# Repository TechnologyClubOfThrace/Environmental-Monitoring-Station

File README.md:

### Περιβαλλοντικός σταθμός επιτήρησης

Ο περιβαλλοντικός σταθμός επιτήρησης ειναι μια κατασκευή βασισμένη στο arduino και σε ανοιχτές τεχνολογίες με σκοπό την καταγραφή περιβαλλοντικών μετρήσεων, όπως ενδεικτικά, η ποιότητα του αέρα που αναπνέουμε, η καθαρότητα του νερού που πίνουμε, τα επίπεδα της ραδιενέργειας και η ηλεκτρομαγνητική ακτινοβολία.

Στην Ελλάδα πέρα απο κάποιες μετρήσεις για την ατμοσφαιρική ρύπανση που γίνονται κυρίως στην Αθήνα και την θεσσαλονίκη, δεν γνωρίζουμε σε πραγματικό χρόνο τι συμβαίνει στην ατμόσφαιρα.

Καθώς αναπτύσουμε τον σταθμό, ανεβάζουμε και τα δεδομένα που συλλέγονται από τους αισθητήρες εδώ: [Environmental Monitoring Station Live Experimental URL](http://iot.techthrace.com:8080/dashboard/c0007be0-88fe-11eb-8796-2726fafed088?publicId=e1c6fd00-e92f-11e9-a846-0761562e699c)

### Το hardware
Η κατασκευή βασίζεται στο [ESP32-DevKitC](https://www.espressif.com/en/products/hardware/development-boards "ESP32-DevKitC") που εχει ενσωματωμένο WiFi ώστε να μπορούμε να αποστείλουμε τα δεδομένα στον [Thingboard IoT server](https://thingsboard.io/ "Thingboard IoT server"). Όλοι οι αισθητήρες που ενδέχεται να χρησιμοποιηθούν βρίσκονται στην ενότητα [Προμήθεια Hardware](#προμήθεια-hardware)

###### Ενδεικτικά κάποιοι αισθητήρες που θα χρησιμοποιηθούν:

    Αισθητήρας μικρόσωματιδίων MP 10 και MP 2.5
    Αισθητήρας αζώτου
    Αισθητήρας διοξειδίου του άνθρακα
    Αισθητήρας μονοξειδίου του άνθρακα
    Αισθητήρας UV ακτινοβολίας
    Αισθητήρας θερμοκρασίας
    Αισθητήρας υγρασίας
    Αισθητήρας ατμοσφαιρικής πίεσης 

Οταν θα εχει ολοκληρωθεί η σύνδεση των αισθητήρων θα δημοσιεύσουμε εδώ αναλυτικές οδηγίες σχετικά με τον τρόπο σύνδεσης στο ESP32 ώστε να μπορει οποίος θέλει να κατασκευάσει τον δικό του σταθμό και αν θέλει να στέλνει τα δεδομένα στον υπάρχον IoT server για να εχουμε μια ακομα καλύτερη εικόνα του περιβάλλοντος απο διάφορες περιοχές.

### Το software 
Ο κώδικας που τρέχει στο ESP32 βρίσκεται μέσα στο φάκελο [src/EnvironmentalMonitoringStation](https://github.com/TechnologyClubOfThrace/Environmental-Monitoring-Station/tree/master/src/EnvironmentalMonitoringStation "src/EnvironmentalMonitoringStation") και μπορείτε να τον ανοίξετε με το Arduino IDE.

Για να γινει compile θα πρεπει να εγκαταστήσετε αρχικά τους οδηγούς για το ESP32 και στη συνεχεια και όλα τα header files που θα σας εμφανίσει οτι λείπουν το Arduino IDE. Τα header files θα πρεπει να τα αντιγράψετε απο τον φάκελο arduino_libraries μέσα στο φάκελο libraries του Arduino IDE. Την τοπική διαδρομή στο μηχάνημα σας μπορείτε να την δείτε απο τα preferences του Arduino IDE.

Πέρα απο το λογισμικό που τρέχει μέσα στο ESP32, υπάρχει και το server side κομμάτι όπου συλλέγονται και παρουσιάζονται όλες οι μετρήσεις του σταθμού. Για τον σκοπό χρησιμοποιούμε το [Thingsboard](https://thingsboard.io/ "Thingsboard") το οποίο εχουμε εγκαταστήσει στον Debian GNU/Linux server του συλλόγου. 

#### Το dashboard όπου απεικονίζονται όλα τα δεδομένα που συλλέγονται είναι διαθέσιμο από [εδώ](http://iot.techthrace.com:8080/dashboard/c0007be0-88fe-11eb-8796-2726fafed088?publicId=e1c6fd00-e92f-11e9-a846-0761562e699c)

### Συμμετοχή στην ανάπτυξη
Για την επεξεργασία αρχείων .md χρησιμοποιούμε συνήθως το [https://pandao.github.io/editor.md](https://pandao.github.io/editor.md "https://pandao.github.io/editor.md")

### Ατμοσφαιρική ρύπανση
Η ευρωπαϊκή επιτροπή εχει δημοσιεύσει αναλυτικά τα επιτρεπτά όρια σχετικά με την ατμοσφαιρική ρύπανση.
[EU Air Quality Standards](http://ec.europa.eu/environment/air/quality/standards.htm "EU Air Quality Standards")

United Stated Environmental Protection Agency - [NAAQS Table](https://www.epa.gov/criteria-air-pollutants/naaqs-table "NAAQS Table")

USA Labor Department - [Ποιότητα αέρα εσωτερικών χώρων](https://www.osha.gov/SLTC/indoorairquality/ "Ποιότητα αέρα εσωτερικών χώρων")

### Σταθμοί παρακολούθησης της ατμοσφαιρικής ρύπανσης σε όλο τον κόσμο
[European Air Quality Index](http://airindex.eea.europa.eu/ "European Air Quality Index")

[World's Air Pollution: Real-time Air Quality Index](https://waqi.info/ "World's Air Pollution: Real-time Air Quality Index")
Ο συγκερκιμένος οργανισμός εχει αναλάβει την κατασκευή σταθμών και τη συλλογή δεδομένων τους. [Εχει δημοσιεύσει και αρκετά στοιχεια](https://aqicn.org/sensor/ "Εχει δημοσιεύσει και αρκετά στοιχεια") σχετικά με τους αισθητήρες που χρηαιμοποιουνται. Κάποιους απο αυτούς τους αισθητήρες τους χρησιμοποιούμε και εμείς.

[https://opensensemap.org](https://opensensemap.org "https://opensensemap.org")
Ο συγκεκριμένος οργανισμός κατασκευάζει και τον περιβαλλοντικό σταθμό αισθητήρων **senseBox** και έχει δημοσιεύσει αναλυτικά τους αισθητήρες που χρησιμοποιεί εδώ: [https://www.sensebox.de/en/products](https://www.sensebox.de/en/products "https://www.sensebox.de/en/products")

[http://safecast.org/tilemap/](http://safecast.org/tilemap/ "http://safecast.org/tilemap/")
Ο [οργανισμός SafeCast](https://blog.safecast.org "οργανισμός SafeCast") δημιουργήθηκε από εθελοντές μετά το πυρηνικό ατύχημα στη Fucushima το 2011. Έχουν κατασκευάσει περιβαλλοντικούς σταθμούς καταγραφής  των επιπέδων της ραδιενέργειας και άλλων δεδομένων και έχουν ανεβάσει τα πάντα στο [github ώς open source και open hardware](https://github.com/Safecast "github ώς open source και open hardware").
Τα kit των συσκευών υπάρχουν εδώ: [https://github.com/Safecast/General/wiki/Safecast-Devices](https://github.com/Safecast/General/wiki/Safecast-Devices "https://github.com/Safecast/General/wiki/Safecast-Devices")

[http://maps.luftdaten.info/](http://maps.luftdaten.info/ "http://maps.luftdaten.info/")
 Πληροφορίες για την κατασκευή του **Fine Dust Sensor** που αποστέλει δεδομένα για τον παραπάνω χάρτη υπάρχουν εδώ: [https://luftdaten.info/en/construction-manual/](https://luftdaten.info/en/construction-manual/ "https://luftdaten.info/en/construction-manual/")

[EPA AirData Air Quality Monitors](https://epa.maps.arcgis.com/apps/webappviewer/index.html?id=5f239fd3e72f424f98ef3d5def547eb5&extent=-146.2334,13.1913,-46.3896,56.5319 "EPA AirData Air Quality Monitors")
Δεδομένα που συλλέγονται από το [United Stated Environmental Protection Agency](https://www.epa.gov/outdoor-air-quality-data/interactive-map-air-quality-monitors "United Stated Environmental Protection Agency")

### Προμήθεια hardware
Παρακάτω είναι οι δύο πίνακες με την αναλυτική περιγραφή του κόστους καθώς και σύνδεσμοι αγοράς για τους αισθητήρες και τα υλικά που χρειάζονται για την κατασκευή του σταθμού.

###### Πίνακας 1

|  Αισθητήρας | Μοντέλο | Datasheet | Interface | Κατανάλωση | Arduino API | Κόστος | Αγορά από  |
| ------------ | ------------ | ------------ | ------------ | ------------ | ------------ | ------------ | ------------ |
| Θερμοκρασίας  | DS18B20   | | | | [ΝΑΙ - Library Manager](https://www.arduinolibraries.info/libraries/dallas-temperature)  |  3.50 | [eBay MAKERSHOP](https://www.ebay.com/itm/3x-DS18B20-Wasserdicht-Digital-Temperatur-Fuhler-Sensor-Raspberry-Pi-Arduino/253585471592?hash=item3b0adf3868:g:Wr8AAOSwxLdb3Zdt "eBay MAKERSHOP")  |
| Υγρασίας  | BME280  | [Link](https://cdn-shop.adafruit.com/datasheets/BST-BME280_DS001-10.pdf "Link") | I2C, SPI | [ΝΑΙ - Library Manager](https://www.arduinolibraries.info/libraries/bme280)  | 5.75  | [eBay MAKERSHOP](https://www.ebay.com/itm/BME280-Temperatur-Sensor-Luftdruck-Feuchtigkeit-I2C-5V-Barometer-Arduino-Digital/253107395109?hash=item3aee605a25:g:Ol8AAOSwHWtb3znL "eBay MAKERSHOP") |
| Ατμοσ. πίεσης  | BME280 |  [Link](https://cdn-shop.adafruit.com/datasheets/BST-BME280_DS001-10.pdf "Link") | I2C, SPI | | [ΝΑΙ - Library Manager](https://www.arduinolibraries.info/libraries/bme280) | 5.75 | [eBay MAKERSHOP](https://www.ebay.com/itm/BME280-Temperatur-Sensor-Luftdruck-Feuchtigkeit-I2C-5V-Barometer-Arduino-Digital/253107395109?hash=item3aee605a25:g:Ol8AAOSwHWtb3znL "eBay MAKERSHOP")  |
| Μικροσωματιδίων MP 10 + 2.5 |  PMS7003 | [Link](http://download.kamami.pl/p564008-PMS7003%20series%20data%20manua_English_V2.5.pdf "Link")| UART | ≤100mA | [ΝΑΙ - Github](https://github.com/fu-hsi/PMS) | 15.44 | [Aliexpress](https://www.aliexpress.com/item/PLANTOWER-Laser-PM2-5-DUST-SENSOR-PMS7003-G7-Thin-shape-Laser-digital-PM2-5-sensor-Inculd/32784279004.html?spm=2114.search0604.3.9.14ec3794G5sCkA&ws_ab_test=searchweb0_0,searchweb201602_6_10065_10068_319_10059_10884_317_10887_10696_321_322_10084_453_10083_454_10103_10618_10304_10307_10820_10821_537_10302_536,searchweb201603_52,ppcSwitch_0&algo_expid=fab9744e-8fdf-46f4-a08f-b32e40ab44f8-1&algo_pvid=fab9744e-8fdf-46f4-a08f-b32e40ab44f8 "Aliexpress")  |
| Μονοξειδίου του άνθρακα | MQ-7 | [Link](https://www.sparkfun.com/datasheets/Sensors/Biometric/MQ-7.pdf "Link") | Analog |  130 -150 mA | [ΝΑΙ - Github - Χρειάζεται έλεγχος](https://github.com/swatish17/MQ7-Library) |  3.99 | [eBay MAKERSHOP](https://www.ebay.com/itm/MQ-7-Kohlenmonoxid-Sensor-CO-Gas-Sensor-Modul-Raspberry-Pi-Arduino/252715061610?hash=item3ad6fdd16a:g:OoIAAOSwUpFb4cC4 "eBay MAKERSHOP")  |
| Διοξειδίου του άνθρακα  |  MH-Z19 | [Link](https://www.winsen-sensor.com/d/files/PDF/Infrared%20Gas%20Sensor/NDIR%20CO2%20SENSOR/MH-Z19%20CO2%20Ver1.0.pdf "Link") |UART, PWM | <18 mA | [ΝΑΙ - Library Manager (2 βιβλιοθήκες)](https://www.arduinolibraries.info/libraries/mh-z19) |  18.14 | [Aliexpress](https://www.aliexpress.com/item/MH-Z19-infrared-co2-sensor-for-co2-monitor-carbon-dioxide-sensor-UART-PWM-serial-output-0/32916782044.html?spm=2114.search0604.3.2.131712c0k5jgr2&ws_ab_test=searchweb0_0,searchweb201602_6_10065_10068_319_10059_10884_317_10887_10696_321_322_10084_453_10083_454_10103_10618_10304_10307_10820_10821_537_10302_536,searchweb201603_52,ppcSwitch_0&algo_expid=4933ca2c-6944-4ce4-a4d8-526522e070d7-0&algo_pvid=4933ca2c-6944-4ce4-a4d8-526522e070d7)  |
| Διοξειδίου του άνθρακα  |  MG811 with analog | | | [ΝΑΙ - Github - Θέλει δουλειά το calibration κλπ](https://sandboxelectronics.com/?p=147) |  25.70 | [Aliexpress](https://www.aliexpress.com/item/MG811-Carbon-Dioxide-Gas-CO2-Sensor-Module-Detector-With-Analog-Signal-Output-0-2V/32859295115.html?spm=2114.search0604.3.2.45c515873oy8F8&ws_ab_test=searchweb0_0,searchweb201602_6_10065_10068_319_10059_10884_317_10887_10696_321_322_10084_453_10083_454_10103_10618_10304_10307_10820_10821_537_10302_536,searchweb201603_52,ppcSwitch_0&algo_expid=9a1ea977-22df-4c78-8b9a-8b2115acc860-0&algo_pvid=9a1ea977-22df-4c78-8b9a-8b2115acc860 "Aliexpress")  |
| Διοξειδίου του άνθρακα  |  MG811 | | | [ΝΑΙ - Github - Θέλει δουλειά το calibration κλπ](https://github.com/avkghost/MG811_sensor_library)  |  21.40 | [Aliexpress](https://www.aliexpress.com/item/wholesale-MG811-carbon-dioxide-sensor-CO2-sensor-gas-sensor-module-free-shipping/1160134439.html?spm=2114.search0604.3.9.45c515873oy8F8&ws_ab_test=searchweb0_0,searchweb201602_6_10065_10068_319_10059_10884_317_10887_10696_321_322_10084_453_10083_454_10103_10618_10304_10307_10820_10821_537_10302_536,searchweb201603_52,ppcSwitch_0&algo_expid=9a1ea977-22df-4c78-8b9a-8b2115acc860-1&algo_pvid=9a1ea977-22df-4c78-8b9a-8b2115acc860 "Aliexpress") |
| Αζώτου  | MQ131 πλαστικό (low concentration of ozone)  | | | [ΝΑΙ - Github](https://github.com/ostaquet/Arduino-MQ131-driver) | 14.61 |  | [Aliexpress](https://www.aliexpress.com/item/MQ131-ozone-sensor-ozone-gas-detection-sensor-module-free-shipping/1159957338.html?spm=2114.search0604.3.2.742b79786EZfOC&ws_ab_test=searchweb0_0,searchweb201602_6_10065_10068_319_10059_10884_317_10887_10696_321_322_10084_453_10083_454_10103_10618_10304_10307_10820_10821_537_10302_536,searchweb201603_52,ppcSwitch_0&algo_expid=4e1feea9-1857-43e6-8fb2-2302f84d31eb-0&algo_pvid=4e1feea9-1857-43e6-8fb2-2302f84d31eb "Aliexpress")  |
| NO2 Nitrogen Dioxide Sensor  | ?  | | |  |  |  |  |
| SO2 Sulfur Dioxide sensor | ?  | | |  |  |  |  |
| Ραδιενέργειας |   | | | [ΝΑΙ - Θέλει δουλειά - Υπάρχει παράδειγμα κώδικα](https://rhelectronics.net/store/radiation-detector-geiger-counter-diy-kit-second-edition.html)  | 38.23  | [eBay](https://www.ebay.com/itm/DIY-Nuclear-Radiation-Detector-GM-Assembled-Geiger-Counter-Kit-AHS/303029621778?hash=item468df91412:m:m8ONIcW9PE1UFVKfkgYXmHQ "eBay")|
| Ραδιενέργειας |   | | | [ΝΑΙ - Θέλει δουλειά - Υπάρχει παράδειγμα κώδικα](https://rhelectronics.net/store/radiation-detector-geiger-counter-diy-kit-second-edition.html) | 38.23  | [Aliexpress](https://www.ebay.com/itm/DIY-Nuclear-Radiation-Detector-GM-Assembled-Geiger-Counter-Kit-AHS/303029621778?hash=item468df91412:m:m8ONIcW9PE1UFVKfkgYXmHQ "Aliexpress")|
| Ηχορύπανση | digital  | | | Ψηφιακό μάλον δεν μας κάνει | 1.95 | [eBay MAKERSHOP](https://www.ebay.com/itm/Gerauschsensor-Mikrofon-Sound-Sensor-Modul-Raspberry-Pi-Arduino-Lautstarke/252748930718?hash=item3ad9029e9e:g:2dUAAOSwqRlb4cCg "eBay MAKERSHOP") |
| Ηχορύπανση | analog+digital | | | Χρήση analogRead | 2.90 | [eBay MAKERSHOP](https://www.ebay.com/itm/Analog-Sound-Sensor-Gerauschsensor-Sensor-Mikrofon-Modul-Arduino-Raspberry-Pi/252909274219?hash=item3ae291446b:g:pvcAAOSw2-pb4H2j "eBay MAKERSHOP") |
| Ηχορύπανση | MAX9814 | | | ? | 5.25 | [eBay MAKERSHOP](https://www.ebay.com/itm/MAX9814-Sound-Sensor-Gerauschsensor-Mikrofon-Microphone-Module-Arduino-Raspbe/253890621317?hash=item3b1d0f6f85:g:Y1UAAOSwdrdb6kFF "eBay MAKERSHOP") |

- Για τον αισθητήρα θερμοκρασίας υπάρχουν αναφορές για μή ακριβείς μετρήσεις του BME280 λόγω θέρμανσης του αισθητήρα. Αντί αυτού θα χρησιμοποιήσουμε τον αδιάβροχο DS18B20 γιατί χρειάζεται να βρίσκεται και έξω από το κουτί, εκτεθειμένος. Ο αισθητήρας θερμοκρασίας του BME280 θα χρησιμοποιείται ώς εφεδρικός.

- Για τον αισθητήρα ηχορύπανσης να διαλέξουμε ένα από τους τρείς

- Να προσέξουμε ώστε να υπάρχουν βιβλιοθήκες για την λήψη των μετρήσεων από τους αισθητήρες που θα επιλέξουμε

- Ο αισθητήρας CO2 MH-Z19 πιθανότατα είναι καλύτερος από τον MG811. Το API του έχει τη δυνατότητα αυτόματου calibration,  είναι φθηνότερος, υποστηρίζει το πρωτόκολλο UART, είναι πιο σταθεροποιημένος και έχει 2 βιβλιοθήκες έτοιμες προς χρήση στον library manager του arduino IDE.

- Για τον κώδικα που απαιτείται για λήψη δεδομένων απο το geiger counter, ίσως είναι καλύτερα να δούμε τί έχουν υλοποιήσει στον σταθμό του safecast.org 

- Κάποιοι από τους αισθητήρες θέλουν έρευνα για να καταλάβουμε πώς λειτουργούν και πώς μπορούμε να πάρουμε ακριβείς μετρήσεις, καθώς δεν συνοδεύνται απο API. Για αυτό τον λόγο θα πρέπει να έχουμε ένα πρόχειρο arduino device ώστε να κάνουμε έλεγχο ένα-ένα αυτους αισθητήρες μέχρι να γράψουμε τον σωστό κώδικα. Στη συνέχεια μπορούμε να δημιουργήσουμε ένα library και να το προσφέρουμε και στην κοινότητα των arduino developers.

###### Πίνακας 2

| Υλικό  | Περιγραφή  | Κόστος  | Αγορά από  |
| ------------ | ------------ | ------------ | ------------ |
| ESP32 | Ο μικροελεγκτής όπου συνδέονται όλα. Κατανάλωση 500mA max | 8.35  |  [eBay MAKERSHOP](https://www.ebay.com/itm/Espressif-ESP32-WLAN-Dev-Kit-Board-Development-Bluetooth-Wifi-v1-WROOM32-NodeMCU/253059783728?hash=item3aeb89dc30:g:5-8AAOSwAThb3MaZ "eBay MAKERSHOP")  |
| Jumper wire male-female  |   | 2.49  |  [eBay MAKERSHOP](https://www.ebay.com/itm/Jumper-Wire-Steckbrucken-Steckbrett-Kabel-20p-male-female-mannlich-weiblich/252715145677?hash=item3ad6ff19cd:m:mz_Na6LfgzHzHslqexs0NfQ&var=551695342124 "eBay MAKERSHOP") |
| Jumper wire male-male  |   | 2.49  |   |
| Breadboard 400 | Για τη σύνδεση του ESP32 και των αισθητήρων  | 3.85  |  [eBay MAKERSHOP](https://www.ebay.com/itm/Premium-Steckbrett-400-Kontakte-Breadboard-Transparent-durchsichtig-transparent/252715004864?hash=item3ad6fcf3c0:g:E5wAAOSwXOhb5H0n "eBay MAKERSHOP") |
| Breadboard 830  | Για τη σύνδεση του ESP32 και των αισθητήρων  |  3.75 |  [eBay MAKERHSOP](https://www.ebay.com/itm/MB-102-830-Kontakte-Breadboard-gros-Steckbrett-Raspberry-Pi-Experimentier/252860727462?hash=item3adfac80a6:g:wC4AAOSwn01b3zoN "eBay MAKERHSOP") |

Σύμφωνα με τα παραπάνω, το συνολικό κόστος για την κατασκευή ενός περιβαλλοντικού σταθμού είναι περίπου 130€

Για την αρχική υλοποίηση αρκούν τα υλικά του παρακάτω πίνακα 3, κυρίως λόγω του ότι το API είναι σχετικά εύκολο στην υλοποίηση και μας αρκούν για την περιβαλλοντική παρατήρηση. Στη συνέχεια μπορούμε να παραγγείλουμε και τους άλλους αισθητήρες οι οποίει θα κάνουν τον σταθμό ακόμα καλύτερο αλλά και που αυξάνουν και την πολυπλοκότητα του κώδικα.

###### Πίνακας 3

| Υλικό  | Περιγραφή  | Κόστος  | Αγορά από  |
| ------------ | ------------ | ------------ | ------------ |
| ESP32  | Ο μικροελεγκτής όπου συνδέονται όλα   | 8.35  |  [eBay MAKERSHOP](https://www.ebay.com/itm/Espressif-ESP32-WLAN-Dev-Kit-Board-Development-Bluetooth-Wifi-v1-WROOM32-NodeMCU/253059783728?hash=item3aeb89dc30:g:5-8AAOSwAThb3MaZ "eBay MAKERSHOP")  |
| Τροφοδοτικό mico usb 5v/3A  | Το τροφοδοτικό του ESP32   | 6.09  |  [eBay](https://www.ebay.com/itm/5V-3A-Micro-USB-AC-Adapter-DC-Power-Supply-Charger-For-Raspberry-Pi-Switch-CH/132940358909?hash=item1ef3dce4fd:m:mseD9SU8kSc8es0lGj11DUg)  |
| Jumper wire male-female  | Καλώδια σύνδεσης | 2.49  |  [eBay MAKERSHOP](https://www.ebay.com/itm/Jumper-Wire-Steckbrucken-Steckbrett-Kabel-20p-male-female-mannlich-weiblich/252715145677?hash=item3ad6ff19cd:m:mz_Na6LfgzHzHslqexs0NfQ&var=551695342124 "eBay MAKERSHOP") |
| Jumper wire male-male  |  Καλώδια σύνδεσης | 2.49  |   |
| Breadboard 400 | Για τη σύνδεση του ESP32 και των αισθητήρων  | 3.85  |  [eBay MAKERSHOP](https://www.ebay.com/itm/Premium-Steckbrett-400-Kontakte-Breadboard-Transparent-durchsichtig-transparent/252715004864?hash=item3ad6fcf3c0:g:E5wAAOSwXOhb5H0n "eBay MAKERSHOP") |
| Breadboard 830  | Για τη σύνδεση του ESP32 και των αισθητήρων  |  3.75 |  [eBay MAKERHSOP](https://www.ebay.com/itm/MB-102-830-Kontakte-Breadboard-gros-Steckbrett-Raspberry-Pi-Experimentier/252860727462?hash=item3adfac80a6:g:wC4AAOSwn01b3zoN "eBay MAKERHSOP") |
| DS18B20 | Αισθητήρας Θερμοκρασίας | 3.50 | [eBay MAKERSHOP](https://www.ebay.com/itm/3x-DS18B20-Wasserdicht-Digital-Temperatur-Fuhler-Sensor-Raspberry-Pi-Arduino/253585471592?hash=item3b0adf3868:g:Wr8AAOSwxLdb3Zdt "eBay MAKERSHOP") |
| BME280 | Αισθητήρας Υγρασίας / Ατμοσ. πίεσης | 5.75 | [eBay MAKERSHOP](https://www.ebay.com/itm/BME280-Temperatur-Sensor-Luftdruck-Feuchtigkeit-I2C-5V-Barometer-Arduino-Digital/253107395109?hash=item3aee605a25:g:Ol8AAOSwHWtb3znL "eBay MAKERSHOP") |
| PMS7003 | Αισθητήρας Μικροσωματιδίων MP2.5/10 - (ΠΡΟΣΟΧΗ! Να συμπεριλαμβάνει το καλώδιο σύνδεσης) | 15.44 | [Aliexpress](https://www.aliexpress.com/item/PLANTOWER-Laser-PM2-5-DUST-SENSOR-PMS7003-G7-Thin-shape-Laser-digital-PM2-5-sensor-Inculd/32784279004.html?spm=2114.search0604.3.9.14ec3794G5sCkA&ws_ab_test=searchweb0_0,searchweb201602_6_10065_10068_319_10059_10884_317_10887_10696_321_322_10084_453_10083_454_10103_10618_10304_10307_10820_10821_537_10302_536,searchweb201603_52,ppcSwitch_0&algo_expid=fab9744e-8fdf-46f4-a08f-b32e40ab44f8-1&algo_pvid=fab9744e-8fdf-46f4-a08f-b32e40ab44f8 "Aliexpress")  |
| MQ-7 | Αισθητήρας Μονοξειδίου του άνθρακα | 3.99 | [eBay MAKERSHOP](https://www.ebay.com/itm/MQ-7-Kohlenmonoxid-Sensor-CO-Gas-Sensor-Modul-Raspberry-Pi-Arduino/252715061610?hash=item3ad6fdd16a:g:OoIAAOSwUpFb4cC4 "eBay MAKERSHOP") |
| MH-Z19 | Αισθητήρας Διοξειδίου του άνθρακα | 18.14 | [Aliexpress](https://www.aliexpress.com/item/MH-Z19-infrared-co2-sensor-for-co2-monitor-carbon-dioxide-sensor-UART-PWM-serial-output-0/32916782044.html?spm=2114.search0604.3.2.131712c0k5jgr2&ws_ab_test=searchweb0_0,searchweb201602_6_10065_10068_319_10059_10884_317_10887_10696_321_322_10084_453_10083_454_10103_10618_10304_10307_10820_10821_537_10302_536,searchweb201603_52,ppcSwitch_0&algo_expid=4933ca2c-6944-4ce4-a4d8-526522e070d7-0&algo_pvid=4933ca2c-6944-4ce4-a4d8-526522e070d7) |
|  | Αισθητήρας Ηχορύπανσης | 2.90 | [eBay MAKERSHOP](https://www.ebay.com/itm/Analog-Sound-Sensor-Gerauschsensor-Sensor-Mikrofon-Modul-Arduino-Raspberry-Pi/252909274219?hash=item3ae291446b:g:pvcAAOSw2-pb4H2j "eBay MAKERSHOP") |
|  | Συνολικό κόστος:  | 76.74 |  |

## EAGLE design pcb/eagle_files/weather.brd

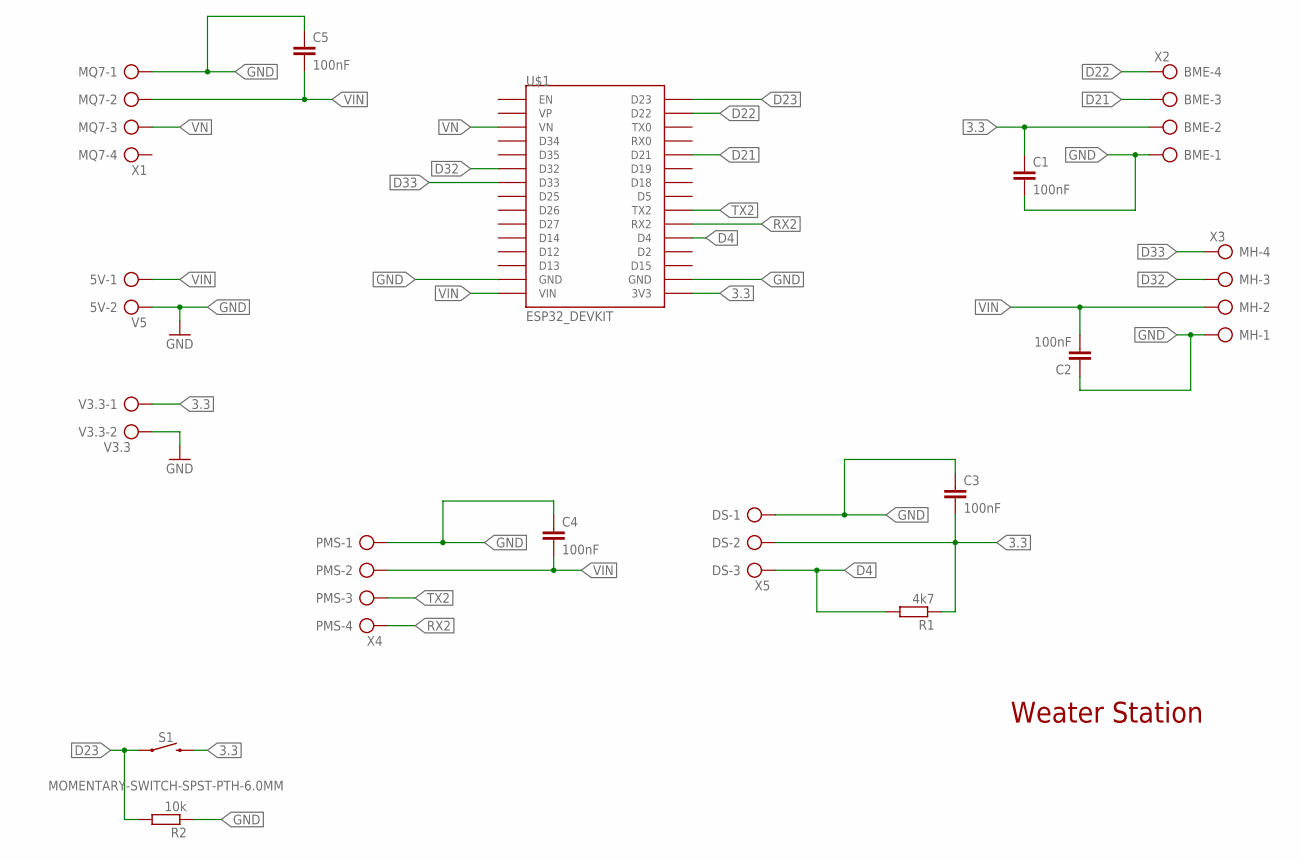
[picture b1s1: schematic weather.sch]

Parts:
5V: V5; AK500/2-H
BME: X2; AK500/4-H
C1, C2, C3, C4, C5: 100nF; C050-025X075
DS: X5; AK500/3-H
MH: X3; AK500/4-H
MQ7: X1; AK500/4-H
PMS: X4; AK500/4-H
R1: 4k7; 0207/10
R2: 10k; 0207/10
S1: MOMENTARY-SWITCH-SPST-PTH-6.0MM; TACTILE_SWITCH_PTH_6.0MM
U$1: ESP32_DEVKIT
V3.3: V3.3; AK500/2-H

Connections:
3.3: BME.2, C1.1, C3.2, DS.2, R1.1, S1.3 (2), U$1.3V3, V3.3.1
D4: DS.3, R1.2, U$1.D4
D21: BME.3, U$1.D21
D22: BME.4, U$1.D22
D23: R2.2, S1.1, U$1.D23
D32: MH.3, U$1.D32
D33: MH.4, U$1.D33
GND: 5V.2, BME.1, C1.2, C2.1, C3.1, C4.1, C5.1, DS.1, MH.1, MQ7.1, PMS.1, R2.1, U$1.GND@1 (GND), U$1.GND@2 (GND), V3.3.2
RX2: PMS.4, U$1.RX2
TX2: PMS.3, U$1.TX2
VIN: 5V.1, C2.2, C4.2, C5.2, MH.2, MQ7.2, PMS.2, U$1.VIN
VN: MQ7.3, U$1.VN

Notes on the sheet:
Weater Station

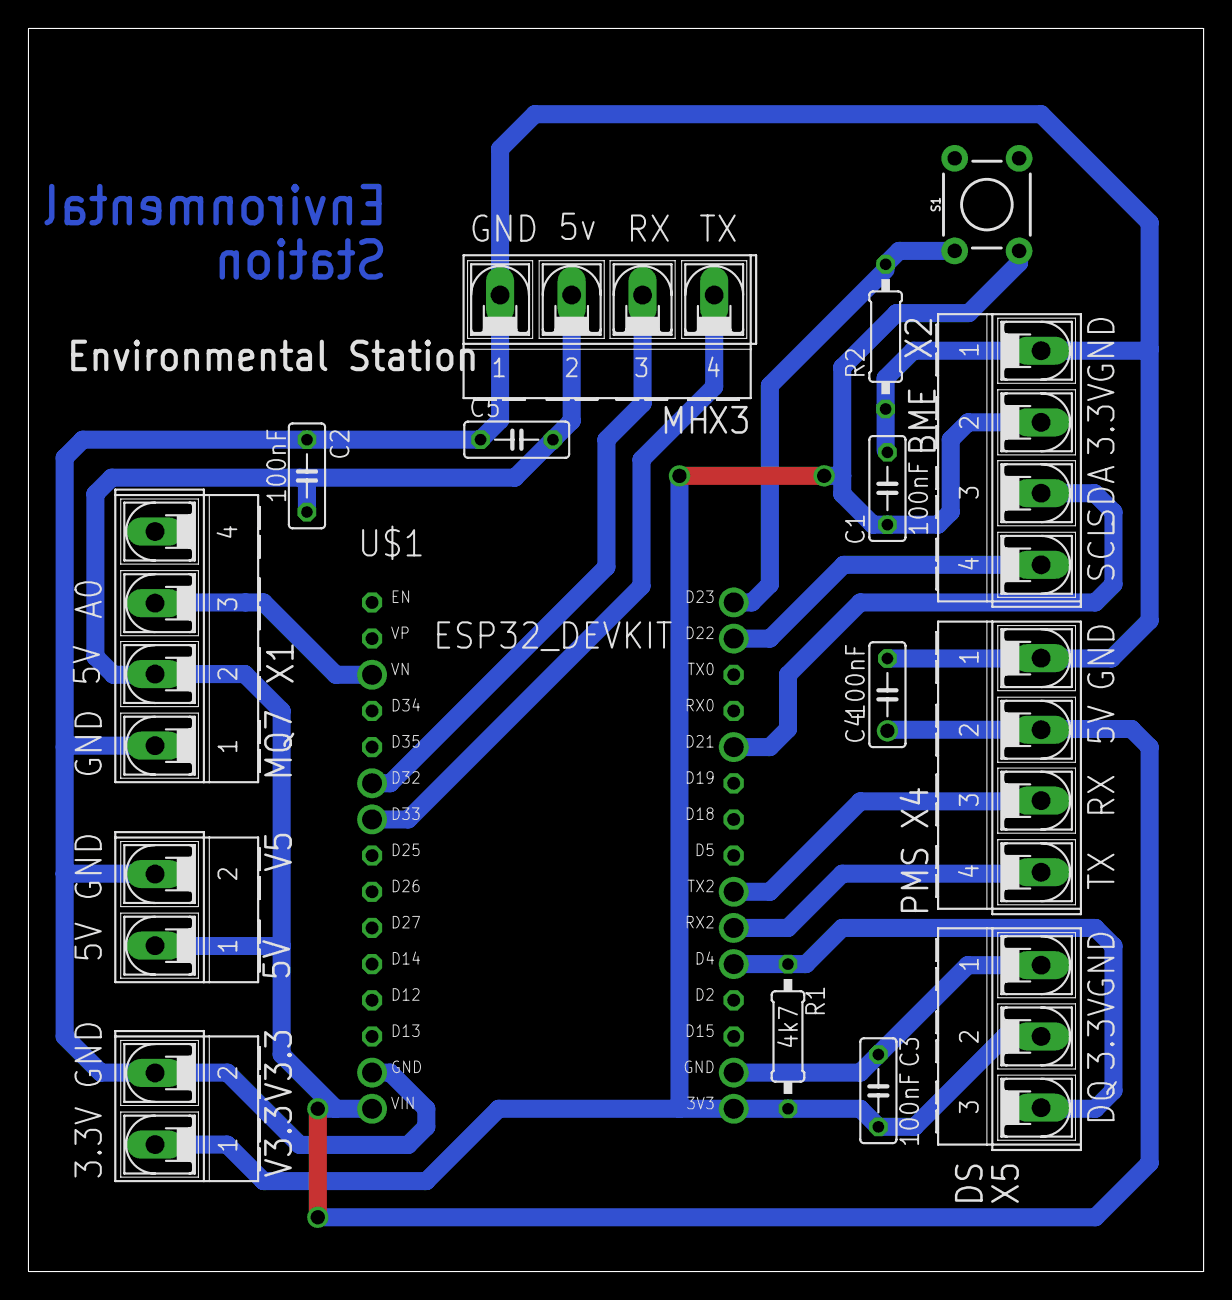
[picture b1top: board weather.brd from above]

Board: 2 copper layers, 82.5 x 87.3 mm, 16 parts (0 on the bottom side), 12 nets.

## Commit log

2019-03-07 Initial commit - 3 sensors, Wifi, push data to IoT Server Thingsboard
2019-03-10 initial station description
2019-03-10 added early station image
2019-03-10 added station image
2019-03-13 Added uptime library and uptime posting to remote IoT server
2019-03-25 Προσθήκη επιπλέον σταθμών ατμοσφαιρικής ρύπανσης
2019-03-26 προσθήκη safecast
2019-04-10 corrected wifi connection issue
2019-04-22 wifi reconnect fixed
2019-05-06 προσθήκη πίνακα αισθητήρων και υλικών
2019-05-06 προσθήκη dashboard link
2019-05-06 προσθήκη στήλης Arduino API
2019-05-06 Προσθήκη συνδέσμων βιβλιοθηκών για κάποιους αισθητήρες
2019-05-06 Προσθήκη αισθητήρα MH-Z19
2019-05-06 Προσθήκη πίνακα 3 (παραγγελίας)
2019-05-06 Προσθήκη Environmental Monitoring Station Live Experimental URL
2019-05-07 Προσθήκη τροφοδοτικού στον πίνακα 3 - παραγγελιών
2019-05-07 Αλλαγή συνολικού κόστους παραγγελίας
2019-05-07 Προσθήκη στηλών Datasheet και Κατανάλωση στον πίνακα των αισθητήρων
2019-05-07 Removed local uptime library files. Using Uptime from library manager
2019-05-07 Αλλαγή στην εισαγωγή
2019-05-07 Προσθήκη αισθητήρων NO2 και SO2
2019-05-10 Προσθήκη ενότητας "Συμμετοχή στην ανάπτυξη"
2019-05-10 Προσθήκη interface και datasheet links
2019-05-16 added esp32 with sensors image
2019-05-29 Προσθήκη αισθητήρων ατμ. πίεσης bme280 και θερμοκρασίας ds18b20
2019-05-30 added the carbon monoxide sensor MQ-7
2019-06-08 Added watchdog feature. BME280 sampling setup. Changed temp sesnor pin to D4
2019-06-13 Added PMS7003 Sensor - Send PM1.0 telemetry data
2019-06-13 Added PM2.5, PM10 measurements
2019-06-17 Προστέθηκε καινούριο και βελτιωμένο σχέδιο
    Καινούρια σύνδεση αισθητήρων, φωτοβολταϊκού με powerbank για πλήρη αυτονομία.
2019-06-24 MQ-7 sensor ppm testing
2019-06-24 minor code refactoring
2019-06-25 added ADC_RESOLUTION const for aqurate CO measurements
2019-06-25 Move the check for wifi connection just before sending data to IoT server
2019-06-26 Better logic for code inside void loop()
2019-09-19 Added CO2 sensor. Troubleshooting PMS and CO2 sensors. Need to use hardwareserial library to read both and print to the console
2019-09-19 Using HardwareSerial libary. All sensors work!
2019-09-19 refactoring
2019-09-20 Use HardwareSerial library for console and other two serial sensors. Fix CO2 and PMS issue.
2019-09-28 MH-Z19 sensor fix using delay workaround. debug mode.
    comments included from previous MHZ19 attempts
2019-09-28 release build
2019-10-01 iotwebconf library preparation for saving configuration data
2019-10-03 refactoring. pms readuntil increase timeout
2019-10-09 Fix of null values returned from pms7003. code refactoring
2019-10-10 Added IotWebConfFactory class for managing station configuration data
2019-10-10 removed clean_eeprom function until we fix it
2019-10-17 Add files via upload
    Βελτιωμένο σχέδιο Περιβαλλοντικού Σταθμού Επιτήρησης
2019-10-19 fix carbon monoxide sensor computation for 3.3V
2019-10-19 added first image of the station with the sensors connected and working!
2019-10-19 change station image
2019-10-21 Rename EnvScaner/readme.md to EnvScanner/readme.md
2019-10-21 Rename EnvScaner/main.py to EnvScanner/main.py
2019-10-23 Διορθώθηκε το σχηματικό διάγραμμα
2019-10-24 Added web server status page and refactor MQ7 sensor code
2019-10-24 Use MQ7 library with 3.3v setting
2020-01-23 minor change
2020-01-23 added MiCS-6814 sensor
    added ability to read:
    - Carbon monoxide
    - Nitrogen dioxide
    - Hydrogen
2020-01-24 Σχηματικό διάγραμμα του σταθμού
2020-01-27 new station url
2020-01-27 Android APP Environmental Monitoring Station V2.
    Environmental Monitoring Station V2. Android εφαρμογή Περιβαλλοντικού σταθμού Επιτήρησης για κινητά και tablets. Version2
2020-01-31 added watchdog - resets arduino after around 60min if post result !=200
2020-01-31 removed unused mypow and old MQ7 sensor code. All where commented
2020-01-31 changed MiCS-6814 and BME280 sensors init order and added delay. Experimental.
2020-05-26 update station url
2020-11-21 Add second iot server log
2021-02-12 set bme280 address manually
2021-03-20 increase delay time before MiCS-6814 setup
2021-03-22 PCB files
    PCB files
    thanks to GreekInventors
    https://greekinventors.gr/
2021-04-04 implement https
2021-04-04 parse firmware upgrade url
2021-04-10 wunderground method
2021-04-10 OTA, IotWebConfFactory 3.0 upgrade
    - esp32 OTA implementation
    - upgrade IotWebConfFactory to major 3.0 - code refactoring based on https://github.com/prampec/IotWebConf/blob/master/doc/MigrationGuide-v3.0.0.md
    -
2021-04-10 define SEND_DATA_TO_WUNDERGROUND, code refactoring
2021-05-07 fix for MiCS-6814 missing sensor
2024-01-25 fix stray character compiler error. Arduino IDE v2 compatibility
2024-02-01 added bme280 temperature reading as a backup in case main temp sensor fails.
    - Upgraded project source for new arduino IDE v2.2.1
    - Upgraded all libraries to the most recent versions
    - Updated firmware version to 1.2 from 1.1
    Here is the build output with all version numbers:
    FQBN: esp32:esp32:esp32
    Using board 'esp32' from platform in folder: /Users/yiannis/Library/Arduino15/packages/esp32/hardware/esp32/2.0.11
2024-02-01 export bootloader
2024-02-01 Remove build directory files
2025-03-28 Upgrade libraries to latest versions. Fixed onewire - dallas temperature sensor reading.
    ESP32 Platform version 3.1.3
    List of libraries used:
    ========================
    Using library IotWebConf at version 3.2.1
    Using library WiFi at version 3.1.3 in folder:
    Using library Networking at version 3.1.3

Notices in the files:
parts and their libraries:
SparkFun-Switches: Licensing: Creative Commons ShareAlike 4.0 International - https://creativecommons.org/licenses/by-sa/4.0
